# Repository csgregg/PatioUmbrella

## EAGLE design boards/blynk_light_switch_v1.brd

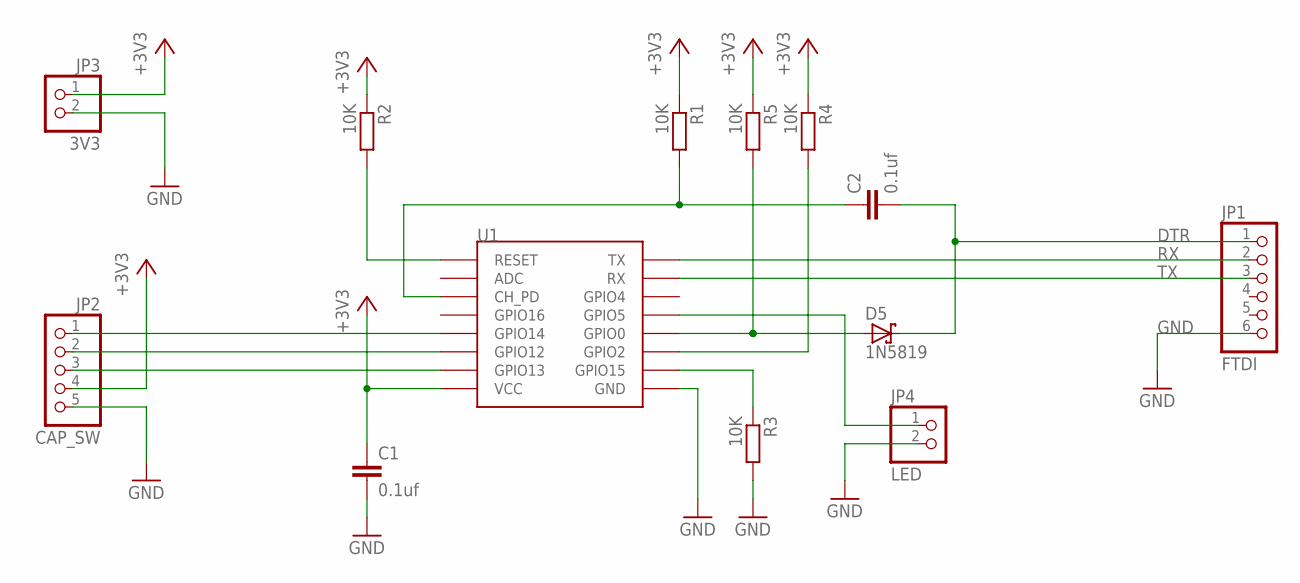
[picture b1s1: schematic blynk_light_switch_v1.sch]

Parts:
C1, C2: 0.1uf; C0805
D5: 1N5819; CB429-17
JP1: FTDI; 1X06
JP2: CAP_SW; 1X05
JP3: 3V3; 1X02
JP4: LED; 1X02
R1, R2, R3, R4, R5: 10K; R0805; MPN MRA0207 100K B 15PPM TA
U1: ESP12SMD; ESP12-SMD

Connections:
+3V3: C1.1, JP2.4, JP3.1, R1.1, R2.1, R4.1, R5.1, U1.VCC
DTR: C2.2, D5.C, JP1.1
GND: C1.2, JP1.6, JP2.5, JP3.2, JP4.2, R3.2, U1.GND
unnamed: R2.2, U1.RESET
unnamed: C2.1, R1.2, U1.CH_PD
unnamed: R4.2, U1.GPIO2
unnamed: JP2.1, U1.GPIO14
unnamed: D5.A, R5.2, U1.GPIO0
unnamed: JP2.2, U1.GPIO12
unnamed: JP2.3, U1.GPIO13
unnamed: R3.1, U1.GPIO15
unnamed: JP4.1, U1.GPIO5
RX: JP1.2, U1.TXD0 (TX)
TX: JP1.3, U1.RXD0 (RX)

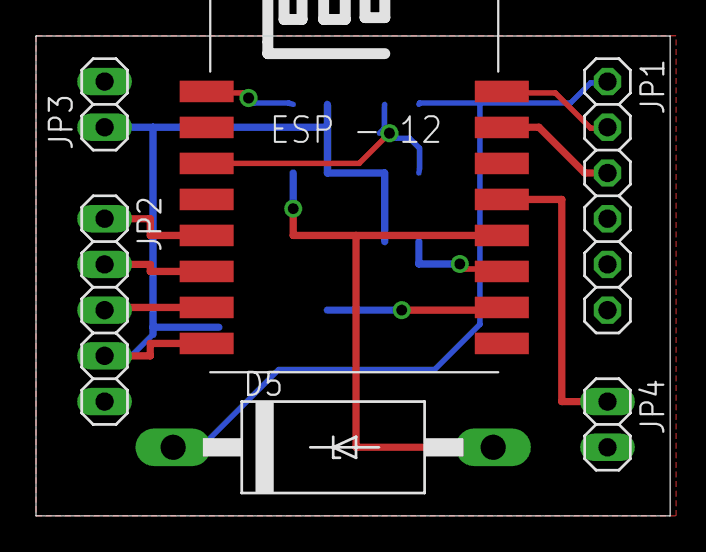
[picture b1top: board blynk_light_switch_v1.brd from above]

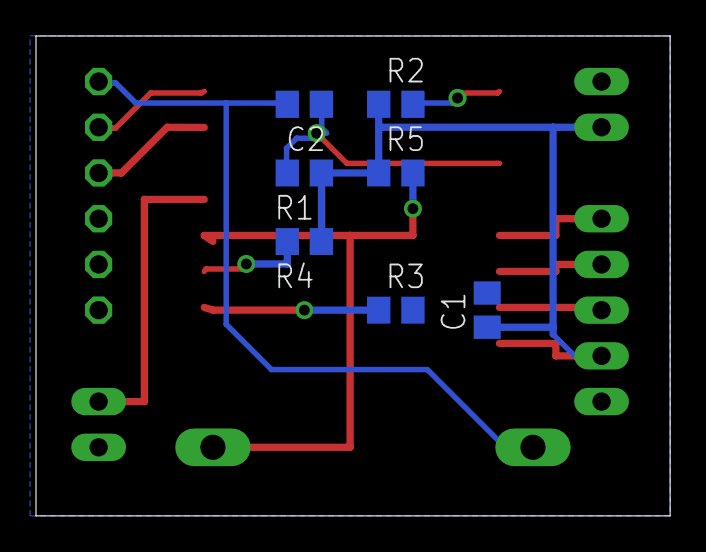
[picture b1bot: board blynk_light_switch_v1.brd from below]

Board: 2 copper layers, 35.2 x 26.7 mm, 13 parts (7 on the bottom side), 14 nets.

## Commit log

2019-11-09 Change .IOC to CPP
